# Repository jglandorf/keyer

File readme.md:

## Two Types of Touch Keyers (Paddles) for CW (Morse Code), Tested on the QMX+  
## Plus, a PTT Microphone PCB for the QMX/QMX+

Implemented for use with the [QMX+ HF transceiver](https://qrp-labs.com/qmxp.html).  
PCBs designed in KiCAD v9.

The first keyer is a [capacitive touch keyer](#capacitive-touch-keyer), based on "Penny Paddles", https://www.thingiverse.com/thing:7049323.

Capacitive touch keyer  

The second keyer is a [pressure paddle](#pressure-sensitive-touch-keyer), based on https://vk3il.net/pressure-paddle-v2/.  

Pressure-sensitive touch keyer  

Thirdly, there is a [PTT microphone PCB](#ptt-microphone-pcb):  

### Capacitive touch keyer  

The capacitive touch paddle is based on KD9AIE's [Penny Paddles](https://www.thingiverse.com/thing:7049323) schematic.  It has been slightly modified:  

The PCB has footprint provisions to use either surface-mount or through-hole components.  Note that a couple members of our local amateur radio club could not get the original schematic to work on a breadboard.  The following two modifications were found to work on the PCB:  
(1)  change the 2N7000 MOSFET to an SI2300 (note that the latter is suface-mount).  There are surely other non-2N7000 devices that are through-hole that will work.  The SI2300's gate drive voltage is about 1.5V lower than the 2N7000's.  
(2)  add a 2M- to 4M-ohm pull-down resistor to each MOSFET's gate. These can be placed on top of C11 and C12 (surface-mount), _or_ use the through-hole pad at C1, C2.  This change was needed to prevent continuous false triggers.  
Pull-down resistors mounted on top of C11, C12:  

Pull-down resistors mounted in pads for C1, C2:  

### Pressure-sensitive touch keyer  

The pressure-sensitive paddle is based on [VK3IL's 'Pressure Paddle' schematic](https://vk3il.net/pressure-paddle-v2/), with minor modifications by [UD6ARJ](https://telegra.ph/CW-key-05-25): 
  
UD6ARJ's modification adds two diodes (D1/D11, D2/D12 above), but I have not yet tested these.  As with the touch keyer, the PCB has footprint provisions to use either surface-mount or through-hole components.  

Although the force-sense resistor leads appear to be designed for through-hole mounting, the PCB has been set up for the leads to be tack-soldered, surface-mount style, so that the FSRs will sit on the PCB as flat as possible, and to avoid interference between the front/back FSRs.  
Note that the leads were slightly longer than expected.    The FSrs may be soldered, as-is, with a bit of insulating varnish under the exposed leads:  
  
or, the excess lead lengths may simply be cut off:  

Most suppliers of the RP-C18.3-ST FSRs charge around $4-5 each, plus shipping (even AliExpress).  If you're willing to buy 10 of them, they can be had on [Alibaba](www.alibaba.com/trade/search?&SearchText=RP-C18.3-ST) for $15-$20 total, including shipping.  The FSRs used for the prototype is from [this supplier](https://www.alibaba.com/product-detail/Intelligent-FSR-402-Thin-Film-Pressure_1600649457578.html).

### Swapping the Keyer Paddle 'dit' and 'dah'  

Radios like the QMX have a menu setting to swap the 3.5mm plug's ring and tip ('dit and 'dah) in software.  If desired, this may be electrically swapped on both PCBs using the solder bridge jumpers.  On each solder jumper, place a solder bridge over the open pads, and cut the short trace segment, near the silkscreen arrow indicator.  

### PTT Microphone PCB  
The QMX/QMX+ uses an external microphone for single sideband (SSB).  This PCB mounts the electret microphone, a push-to-talk (PTT) switch, and a 3.5mm, 3-pin, "TRS" audio jack.  A 3.5mm TRS audio cable (not shown) connects between the PCB and the QMX/QMX+ front panel. 

Bill-of-materials:  
[html BOM ](bom/qmxMic_0.1.html) with component placement pictorial  

| Reference | P/N |  Description | Link |  
| --- | --- | --- | ---- |  
| J1 | PJ-313 | 3.5mm TRS receptacle | [AliExpress](https://www.aliexpress.us/item/3256806149850933.html) |  
| MK1 | AOM-5024L-HD-F-R | _official_ microphone | [Mouser](https://www.mouser.com/ProductDetail/PUI-Audio/AOM-5024L-HD-F-R?qs=GedFDFLaBXHwFCQszj3hAw%3D%3D) |  
| MK2 | MW042502-1 | †_alternate_ mic | [Mouser](https://www.mouser.com/ProductDetail/DB-Unlimited/MW042502-1?qs=wT7LY0lnAe2ReVyhYwHtvg%3D%3D) |  
|     | ???     | *very low cost _alternate_ mic, EOENKK | [AliExpress](https://www.aliexpress.us/item/3256805663549426.html) |  
| SW1 | ‡ | 6x6mm tactile switch | [AliExpress kit](https://www.aliexpress.us/item/3256806914965075.html) |  
| J2 | --- | 2-pin header, 0.1" | ---- |  
| --- | --- | 3.5mm-to-3.5mm M-M audio cable | ---- |   

†This 4.6mm diameter _alternate_ mic is yet to be tested.  It comes with ~100mm wire leads soldered on.  Cost is about half the _official_ mic.  
*This 6mm diameter _alternate_ mic has only been tested in the QMX+ terminal.  Cost is about one fifteenth that of the _official_ mic.  
‡9.5mm total-height tactile switch is shown in photos; ~4.3mm total-height switch is shown in the 3D image above.  9.5mm is very close to the 9.7mm diameter of the _official_ microphone. These switches are commonly available with total heights of 4.3/5/6/7/8/9/10/11/12/13mm and longer.  

Schematic:  
"MK2" is a smaller, less expensive alternate microphone (_to be tested_).  
J3, J4, and J5 are alternate mounting pads for either microphone.  
For potential use with other radios, the 3.5mm jack's 'tip' and 'ring' terminals may  be swapped via the solder bridges JP1 and JP2.

Assembly:  

Note that the 3.5mm jack and the PTT tactile switch may be mounted on either side of the PCB.  __Before soldering, press-fit them in various combinations of front- and back-side mounting, until you find an arrangement to your liking.__  
If using J2 (2x 0.1" pin header) to mount the microphone, bend the pins slightly outward as shown.  __When soldering the mic, be sure that J2's pins do not short to mic's metal housing.  Make sure the housing does not short to any nearby pads.__

Very low-cost [AliExpress](https://www.aliexpress.us/item/3256805663549426.html) mic:  
Top PCB's tactile switch is 7mm.  Bottom PCB's tactile switch is 5mm, which matches the height of the audio jack.  

The QMX+ mic gain setting (see "Set-up with QMX", below) for the very low cost mic needed to be about 10dB higher than for the "official" mic.  

Set-up with QMX  

Setup for the microphone is described in section 5.11 "SSB menu" of the [QMX Operation manual](https://qrp-labs.com/images/qmx/manuals/operation_1_02_006.pdf).  Refering to the "Mic AGC submenu", __be sure to set _Input_ to _Ext. mic_.__  An alternative test using the built-in terminal app is described in the manual's section 8.6.9 "microphone test".

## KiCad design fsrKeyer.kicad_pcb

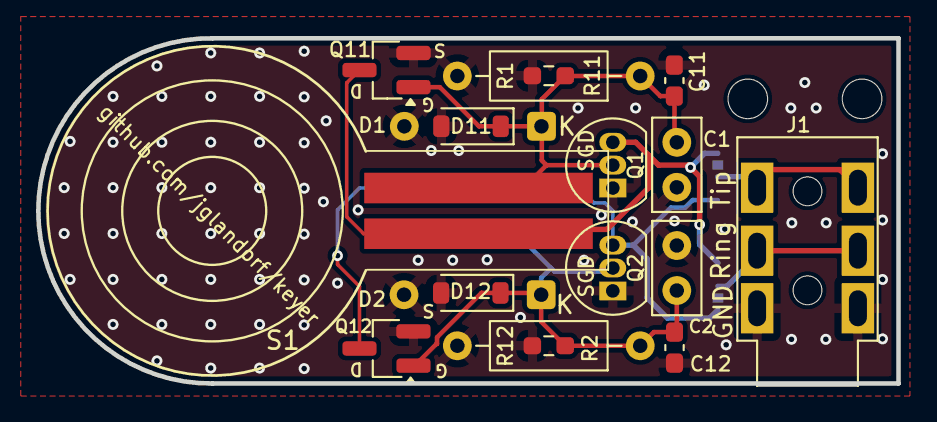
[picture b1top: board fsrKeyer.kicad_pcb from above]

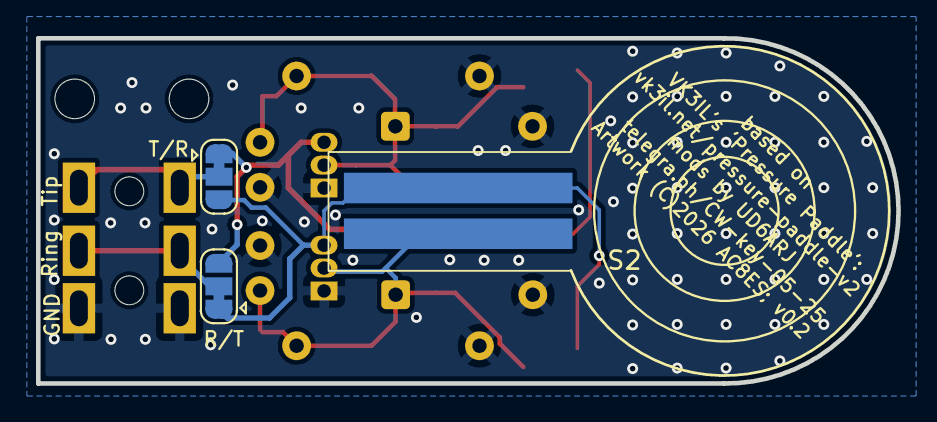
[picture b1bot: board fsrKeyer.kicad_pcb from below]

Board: 2 copper layers, 47.8 x 19.2 mm, 23 parts (3 on the bottom side), 7 nets.

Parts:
C1, C2: 10n; C_Disc_D5.0mm_W2.5mm_P2.50mm
C11, C12: 10n; C_0603_1608Metric_Pad1.08x0.95mm_HandSolder
D1, D2: 1N4148; D_DO-35_SOD27_P7.62mm_Horizontal_UseWSMD
D11, D12: 1N4148W; D_SOD-123
H1, H2: M2.2; MountingHole_2.2mm_M2_DIN965
J1: AudioJack3; Jack_3.5mm_AliExpress_Horizontal
JP1: T/R; SolderJumper-3_P1.3mm_Bridged12_RoundedPad1.0x1.5mm
JP2: R/T; SolderJumper-3_P1.3mm_Bridged12_RoundedPad1.0x1.5mm
Q1, Q2: 2N7000; TO-92_Inline_SGD
Q11, Q12: SI2300; SOT-23_MOSFET_GSD_Handsoldering
R1, R2: 470k; R_Axial_DIN0207_L6.3mm_D2.5mm_P10.16mm_Horizontal
R11, R12: 470k; R_0603_1608Metric_Pad0.98x0.95mm_HandSolder
S1, S2: RP-C18.3-ST; FSR_RP-C18.3-ST_RP-C10ST_SMD

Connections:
/Q1G: C1.1, C11.1, D1.1 (K), D11.1 (K), Q1.2 (G), Q11.1 (G), R1.1, R11.1, S1.2
/Q2G: C2.1, C12.1, D2.1 (K), D12.1 (K), Q2.2 (G), Q12.1 (G), R2.1, R12.1, S2.2
/Ring: JP1.3 (B), JP2.1 (A), Q2.3 (D), Q12.3 (D), S2.1
/RingSel: J1.R, JP2.2 (C)
/Tip: JP1.1 (A), JP2.3 (B), Q1.3 (D), Q11.3 (D), S1.1
/TipSel: J1.T, JP1.2 (C)
GND: C1.2, C2.2, C11.2, C12.2, D1.2 (A), D2.2 (A), D11.2 (A), D12.2 (A), J1.S, Q1.1 (S), Q2.1 (S), Q11.2 (S), Q12.2 (S), R1.2, R2.2, R11.2, R12.2

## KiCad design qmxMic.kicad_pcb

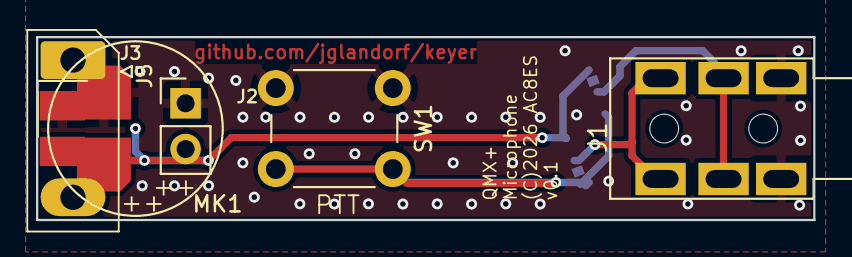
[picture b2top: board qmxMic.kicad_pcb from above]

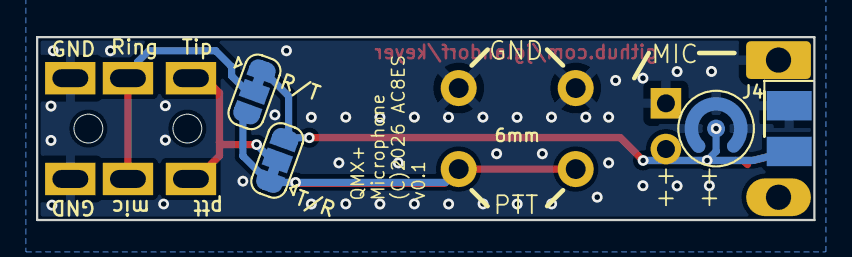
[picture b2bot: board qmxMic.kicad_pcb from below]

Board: 2 copper layers, 43.2 x 10.2 mm, 10 parts (4 on the bottom side), 5 nets.

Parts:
J1: PJ-313; Jack_3.5mm_AliExpress_Horizontal
J2: 2.54mm; PinHeader_1x02_P2.54mm_Vertical
J3: 1.27mm; PinHeader_1x02_P2.54mm_P1.27mm_Vertical_SMD
J4: 2.54mm; PinHeader_1x02_P2.54mm_P1.27mm_Vertical_SMD
J5: 7.62mm; PinHeader_1x02_P7.62mm_Vertical
JP1: T/R; SolderJumper-3_P1.3mm_Bridged12_RoundedPad1.0x1.5mm
JP2: R/T; SolderJumper-3_P1.3mm_Bridged12_RoundedPad1.0x1.5mm
MK1: AOM-5024L-HD-F-R; PUI_AOM-5024L-HD-F-R-SMT
MK2: AOM-5024L-HD-F-R; CUI_CMC-4013-SMT_270
SW1: 6mm; SW_PUSH_6mm

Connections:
/RingSel: J1.R, JP2.2 (C)
/Ring_Mic: J2.2, J3.2, J4.2, J5.2, JP1.3 (B), JP2.1 (A), MK1.2 (+), MK2.2 (+)
/TipSel: J1.T, JP1.2 (C)
/Tip_PTT: JP1.1 (A), JP2.3 (B), SW1.2
GND: J1.S, J2.1, J3.1, J4.1, J5.1, MK1.1 (-), MK2.1 (-), SW1.1

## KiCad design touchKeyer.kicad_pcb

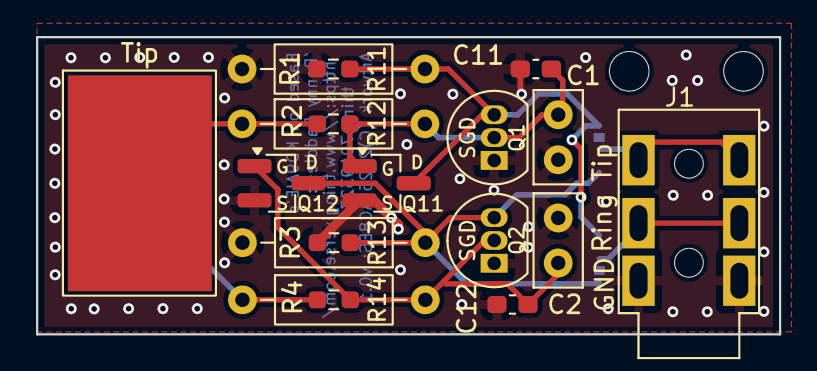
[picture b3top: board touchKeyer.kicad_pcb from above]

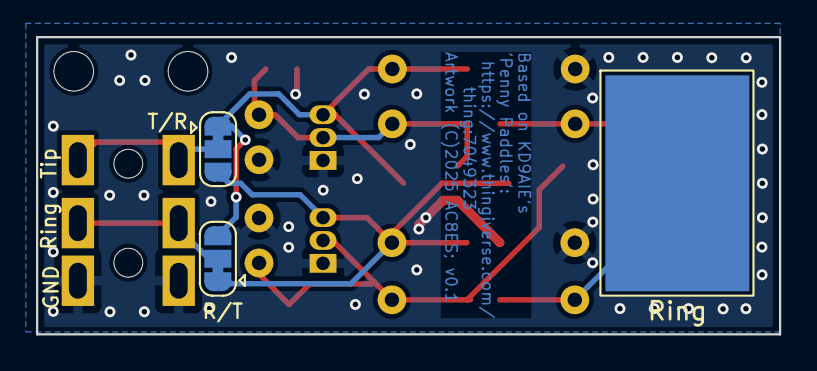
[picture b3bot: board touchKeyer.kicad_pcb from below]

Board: 2 copper layers, 41.3 x 16.5 mm, 23 parts (3 on the bottom side), 9 nets.

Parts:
C1, C2: 330p; C_Disc_D5.0mm_W2.5mm_P2.50mm
C11, C12: 330p; C_0603_1608Metric_Pad1.08x0.95mm_HandSolder
H1, H2: M2.2; MountingHole_2.2mm_M2_DIN965
J1: PJ-313; Jack_3.5mm_AliExpress_Horizontal
JP1: T/R; SolderJumper-3_P1.3mm_Bridged12_RoundedPad1.0x1.5mm
JP2: R/T; SolderJumper-3_P1.3mm_Bridged12_RoundedPad1.0x1.5mm
Q1, Q2: 2N7000; TO-92_Inline_SGD
Q11, Q12: Si2300; SOT-23_MOSFET_GSD_Handsoldering
R1, R3: 10M; R_Axial_DIN0207_L6.3mm_D2.5mm_P10.16mm_Horizontal
R2, R4: 1M; R_Axial_DIN0207_L6.3mm_D2.5mm_P10.16mm_Horizontal
R11, R13: 10M; R_0603_1608Metric_Pad0.98x0.95mm_HandSolder
R12, R14: 1M; R_0603_1608Metric_Pad0.98x0.95mm_HandSolder
TP1: Tip; TestPoint_Pad_8.0x12.0mm
TP2: Ring; TestPoint_Pad_8.0x12.0mm

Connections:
/G1: C1.1, C11.1, Q1.2 (G), Q11.1 (G), R2.2, R12.2
/G2: C2.1, C12.1, Q2.2 (G), Q12.1 (G), R4.2, R14.2
/Ring: JP1.3 (B), JP2.1 (A), Q2.3 (D), Q12.3 (D), R3.1, R13.1
/RingSel: J1.R, JP2.2 (C)
/TP1: R2.1, R12.1, TP1.1
/TP2: R4.1, R14.1, TP2.1
/Tip: JP1.1 (A), JP2.3 (B), Q1.3 (D), Q11.3 (D), R1.1, R11.1
/TipSel: J1.T, JP1.2 (C)
GND: C1.2, C2.2, C11.2, C12.2, J1.S, Q1.1 (S), Q2.1 (S), Q11.2 (S), Q12.2 (S), R1.2, R3.2, R11.2, R13.2

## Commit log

2025-12-08 Initial commit for working prototypes
2025-12-08 Add readme.md
2025-12-08 Add image of solder jumpers. Update readme.md.
2025-12-09 Add FSR image.
2025-12-09 Add schematic snippet.
2025-12-09 Add touch keyer schematic snippet.
2025-12-09 Fix typo.
2025-12-12 Add link to FSR supplier in readme.md.
2026-01-27 Add qmxMic PCB: PUI electret mic to 3.5mm receptacle for the QMX/QMX+ - include .step and .stl models of PCB with mic vertical and horizontal, and with a 'wide' version (== 12.7mm, as this is DKRed's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
2026-02-14 Update 'readme.md' to include the qmxMic PCB. Mark unused connectors as 'dnp'. Fix copyright year.
2026-02-15 Fix typos.
2026-04-22 Added notes for very low-cost microphone from AliExpress.
2026-04-22 Add AliExpress mic specs.
2026-04-24 Accommodate smaller and/or shorter and/or longer sensors. Gerbers sent to DKRed for fabrication.
2026-04-24 Was missing fsrKeyer.kicad_pcb. Checking in v0.1
2026-04-24 Check in v0.2 of fsrKeyer.kicad_pcb.

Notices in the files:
fsrKeyer.kicad_pcb:
Artwork (C)2026 AC8ES
qmxMic.kicad_pcb:
(C)2026 AC8ES
touchKeyer.kicad_pcb:
Artwork (C)2025 AC8ES
Artwork (C)2025 AC8ES; v${REVISION}
